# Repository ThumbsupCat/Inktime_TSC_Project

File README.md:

# Inktime_TSC_Project

## Cuprins:

1. Hardware: - Schematicul si pcb-ul
2. Manufacturing: - Bill of Materials si Pick & Place
3. Mechanical: fisierele 3D
4. Images: Imaginile cu produsul final

## Descriere
InkTime este un ceas smart optimizat pentru autonomie maximă și lizibilitate 
în lumina soarelui. MVP-ul include:

- Display e-paper 1.54" (200×200) cu refresh parțial o dată pe minut
- Notificări BLE de pe telefon cu alertă haptic
- Numărare pași în timp real prin accelerometru cu pedometru integrat
- Încărcare USB-C și programare prin Tag-Connect TC2030 SWD

## Arhitectură
Sistemul este construit în jurul MCU-ului **nRF52840** care integrează 
procesor ARM Cortex-M4 și radio BLE 5.0.
Alimentarea este asigurată de un charger LiPo **BQ25180** conectat la 
USB-C și un regulator buck-boost **RT6160** care menține 3.3V stabil 
pe toată gama de descărcare a bateriei.

## Schema Bloc

## Bill of Materials
| Ref | Component | Package | Funcție | LCSC | Datasheet |
|-----|-----------|---------|---------|------|-----------|
| U1 | nRF52840-QIAA | aQFN73 7×7mm | MCU + BLE 5.0 | [C190794](https://www.lcsc.com/product-detail/C190794.html) | [Datasheet](https://infocenter.nordicsemi.com/pdf/nRF52840_PS_v1.7.pdf) |
| IC1 | BQ25180YBGR | DSBGA-8 | Charger USB-C LiPo | [C3682423](https://www.lcsc.com/product-detail/C3682423.html)| [Datasheet](https://www.ti.com/lit/ds/symlink/bq25180.pdf) |
| IC9 | RT6160AWSC | WLCSP-15 | Regulator 3.3V buck-boost | [C7065276](https://www.lcsc.com/product-detail/C7065276.html) | [Datasheet](https://www.richtek.com/assets/product_file/RT6160A/DS6160A-00.pdf) |
| U3 | MAX17048G+T10 | DFN-8 2×2mm | Fuel gauge LiPo | [C2682616](https://www.lcsc.com/product-detail/C2682616.html) | [Datasheet](https://www.analog.com/media/en/technical-documentation/data-sheets/MAX17048-MAX17049.pdf) |
| IC3 | BMA421 | LGA-12 2×2mm | Accelerometru + pedometru | [C5242966](https://www.lcsc.com/product-detail/C5242966.html) | [Datasheet](https://www.bosch-sensortec.com/media/boschsensortec/downloads/datasheets/bst-bma421-ds000.pdf) |
| IC2 | DRV2605LDGSR | VSSOP-10 | Haptic driver ERM | [C527464](https://www.lcsc.com/product-detail/C527464.html) | [Datasheet](https://www.ti.com/lit/ds/symlink/drv2605l.pdf) |
| D3 | USBLC6-2SC6Y | SOT-363 | Protecție ESD USB | [C2687116](https://www.lcsc.com/product-detail/C2687116.html) | [Datasheet](https://www.st.com/resource/en/datasheet/usblc6-2.pdf) |
| Q1 | DMG2305UX-7 | SOT-323 | PFET EPD power gate | [C370432](https://www.lcsc.com/product-detail/C370432.html) | [Datasheet](https://www.diodes.com/assets/Datasheets/DMG2305UX.pdf) |
| Q3 | SI2301CDS | SOT-23 | PFET EPD gate control | [C10487](https://www.lcsc.com/product-detail/C10487.html) | [Datasheet](https://www.vishay.com/docs/70763/si2301cds.pdf) |
| J4 | KH-TYPE-C-16P | SMD | Conector USB-C | [C165948](https://www.lcsc.com/product-detail/C165948.html) | [Datasheet](https://datasheet.lcsc.com/lcsc/1912111437_Korean-Hroparts-Elec-TYPE-C-31-M-12_C165948.pdf) |
| J1 | 503480-2400 | SMD FPC | Conector display EPD 24 pini | [C393234](https://www.lcsc.com/product-detail/C393234.html) | [Datasheet](https://www.molex.com/pdm_docs/sd/5034802400_sd.pdf) |
| J2 | TC2030-IDC | PTH | Conector debug SWD Tag-Connect | - | [Datasheet](https://www.tag-connect.com/wp-content/uploads/bsk-pdf-manager/TC2030-IDC_1.pdf) |
| ANT1 | 2450AT18B100E | SMD | Antenă 2.4GHz BLE | - | [Datasheet](https://www.johansontechnology.com/datasheets/2450AT18B100E/2450AT18B100E.pdf) |
| L5 | WE-TPC 744042680 | 4828 | Inductor 68µH EPD boost | - | [Datasheet](https://www.we-online.com/catalog/datasheet/744042680.pdf) |
| L7 | FTC252012SR47MBCA | 0603 | Inductor 0.47µH RT6160 | - | - |
| X1 | NT2016SA-32MHz | 3225 | Crystal 32MHz MCU | - | - |
| X2 | Crystal 32.768kHz | 3215 | Crystal RTC | - | - |
| D2, D4, D5 | MBR0530T1G | SOD-123 | Diodă Schottky EPD driver | - | [Datasheet](https://www.onsemi.com/pdf/datasheet/mbr0530t1-d.pdf) |

## Pinii nRF52840

| Pin | Semnal | Componentă | Interfață |
|-----|--------|------------|-----------|
| P0.00/XL1 | XL1 | X2 32.768kHz crystal | Crystal RTC |
| P0.01/XL2 | XL2 | X2 32.768kHz crystal | Crystal RTC |
| P0.02 | SCK | EPD display | SPI |
| P0.03 | MOSI | EPD display | SPI |
| P0.05 | EPD_CS | EPD display | SPI CS |
| P0.06 | SDA | I2C bus (toți senzorii) | I2C |
| P0.07 | SCL | I2C bus (toți senzorii) | I2C |
| P0.08 | IMU_INT1 | BMA421 | GPIO interrupt |
| P0.12 | HAPTIC_EN | DRV2605L | GPIO enable |
| P0.13 | SW_UP | Buton UP | GPIO active-low |
| P0.14 | SW_DN | Buton DOWN | GPIO active-low |
| P0.15 | EPD_DC | EPD display | GPIO data/cmd |
| P0.16 | EPD_RST | EPD display | GPIO reset |
| P0.17 | EPD_BUSY | EPD display | GPIO busy |
| P0.18/RESET | RESET | TC2030 J2 | Hardware reset |
| P0.24 | SWDCLK | TC2030 J2 | SWD debug |
| P0.25 | SWDIO | TC2030 J2 | SWD debug |
| P1.00 | SW_ENT | Buton ENTER | GPIO active-low |
| P1.01 | EPD_3V3 gate | Q1 PFET | GPIO power gate EPD |
| P1.08 | IMU_INT2 | BMA421 | GPIO interrupt |
| VBUS | VBUS | J4 USB-C | USB 5V detect |
| D+ | DP | J4 USB-C | USB data+ |
| D- | DN | J4 USB-C | USB data- |
| ANT | RF | ANT1 2450AT18B100E | 2.4GHz BLE |

## Funcționalitate Hardware

### Power Path
USB-C (5V) → BQ25180 (charger + power path) → RT6160 (buck-boost 3.3V) → toți senzorii și MCU.
LiPo conectat la BQ25180 BAT. MAX17048 măsoară nivelul bateriei prin VBAT.
RT6160 menține 3.3V stabil pe toată gama de descărcare a bateriei (4.2V - 3.0V).

### MCU – nRF52840
Microcontroller ARM Cortex-M4 cu FPU, 64MHz, 1MB flash, 256KB RAM.
BLE 5.0 integrat cu antenă externă 2450AT18B100E plasată la exteriorul PCB-ului cu keepout sub ea.
Programare prin Tag-Connect TC2030 SWD (SWDIO, SWDCLK, RESET).

### Display E-Paper
Conector FPC 24 pini (J1) pentru panou e-paper 1.54" 200x200.
Comunicație SPI: SCK P0.02, MOSI P0.03, CS P0.05, DC P0.15, RST P0.16, BUSY P0.17.
Alimentare VEPD controlată prin PFET Q1 (gate P1.01) pentru power gating.
Circuit driver EPD: inductor L5 68µH, diode Schottky D2/D4/D5, condensatoare boost.

### IMU – BMA421
Accelerometru 3 axe cu pedometru integrat hardware.
Interfață I2C (adresă 0x18), INT1 pe P0.08 pentru wake-on-motion, INT2 pe P1.08.

### Haptic – DRV2605L
Driver motor ERM cu biblioteca de efecte haptic integrate.
Interfață I2C (adresă 0x5A), enable pe P0.12.
Motor ERM conectat direct la OUT+ și OUT-.

### Butoane
3 butoane tactile: UP (P0.13), DOWN (P0.14), ENTER (P1.00).
Configurație active-low cu pull-up intern activat în firmware.

### USB
Conector USB-C cu protecție ESD USBLC6 pe liniile D+/D-.
VBUS conectat la BQ25180 și la pinul de detecție al nRF52840.

### I2C Bus
Shared I2C pe SDA P0.06 / SCL P0.07 la 400kHz.
Dispozitive: BQ25180 (0x6A), RT6160 (0x75), MAX17048 (0x36), BMA421 (0x18), DRV2605L (0x5A).
Pull-up 10kΩ la 3.3V.

## PCB Design Notes

### Stackup
4 layere:
- Layer 1 (Top): semnal + componente SMD
- Layer 2: GND plane
- Layer 3: 3.3V power plane
- Layer 4 (Bottom): semnal

### Decizii de design
- GND rezolvat prin polygon pour pe toate layerele (Top, c2, Bottom)
- 3V3 rezolvat prin polygon pour pe layer-ul c63
- Antena 2450AT18B100E plasată la exteriorul boardului cu decupaj (keepout) 
  sub elementul radiant – fără cupru, fără trasee, fără plane sub antenă
- Condensatoare de decuplare plasate lângă pinii VCC ai fiecărui IC
- BMA421 plasat departe de motorul ERM pentru a evita false step counts
- Trasee de semnal: 0.15mm, trasee de power: 0.3mm

### Erori acceptate în DRC
- **Overlap Via-Smd - 6 erori approved**: via-uri în zona interioară a nRF52840 QFN73 
  din cauza densității extreme a pad-urilor. Nu pot fi rutate altfel in versiunea mea de rutare.
- **Copper Width - 2 erori approved**: trasee înguste (0.1mm) folosite pentru escape routing 
  din zona pinilor interiori ai MCU-ului unde spațiul nu permite 0.15mm.
- **Board Outline Clearance**: cauzate de modelul 3D al conectorului USB-C 
  care depășește ușor outline-ul – nu afectează fabricația.
- **Pad-Solid Polygon Shape, overlap**: footprintul pentru switchuri pe care l-am primit este facut prost.

### Probleme cunoscute
- Pinul RESET al nRF52840 rutat prin via escape din cauza
  poziției interioare în pachetul QFN73.
- Rutarea este foarte densă în zona nRF52840 din cauza 
  numărului mare de pini (73) și a spațiului limitat pe board.
  Acest lucru a necesitat trasee de 0.1mm și via-uri de escape
  pentru pinii din rândurile interioare ale chipului.

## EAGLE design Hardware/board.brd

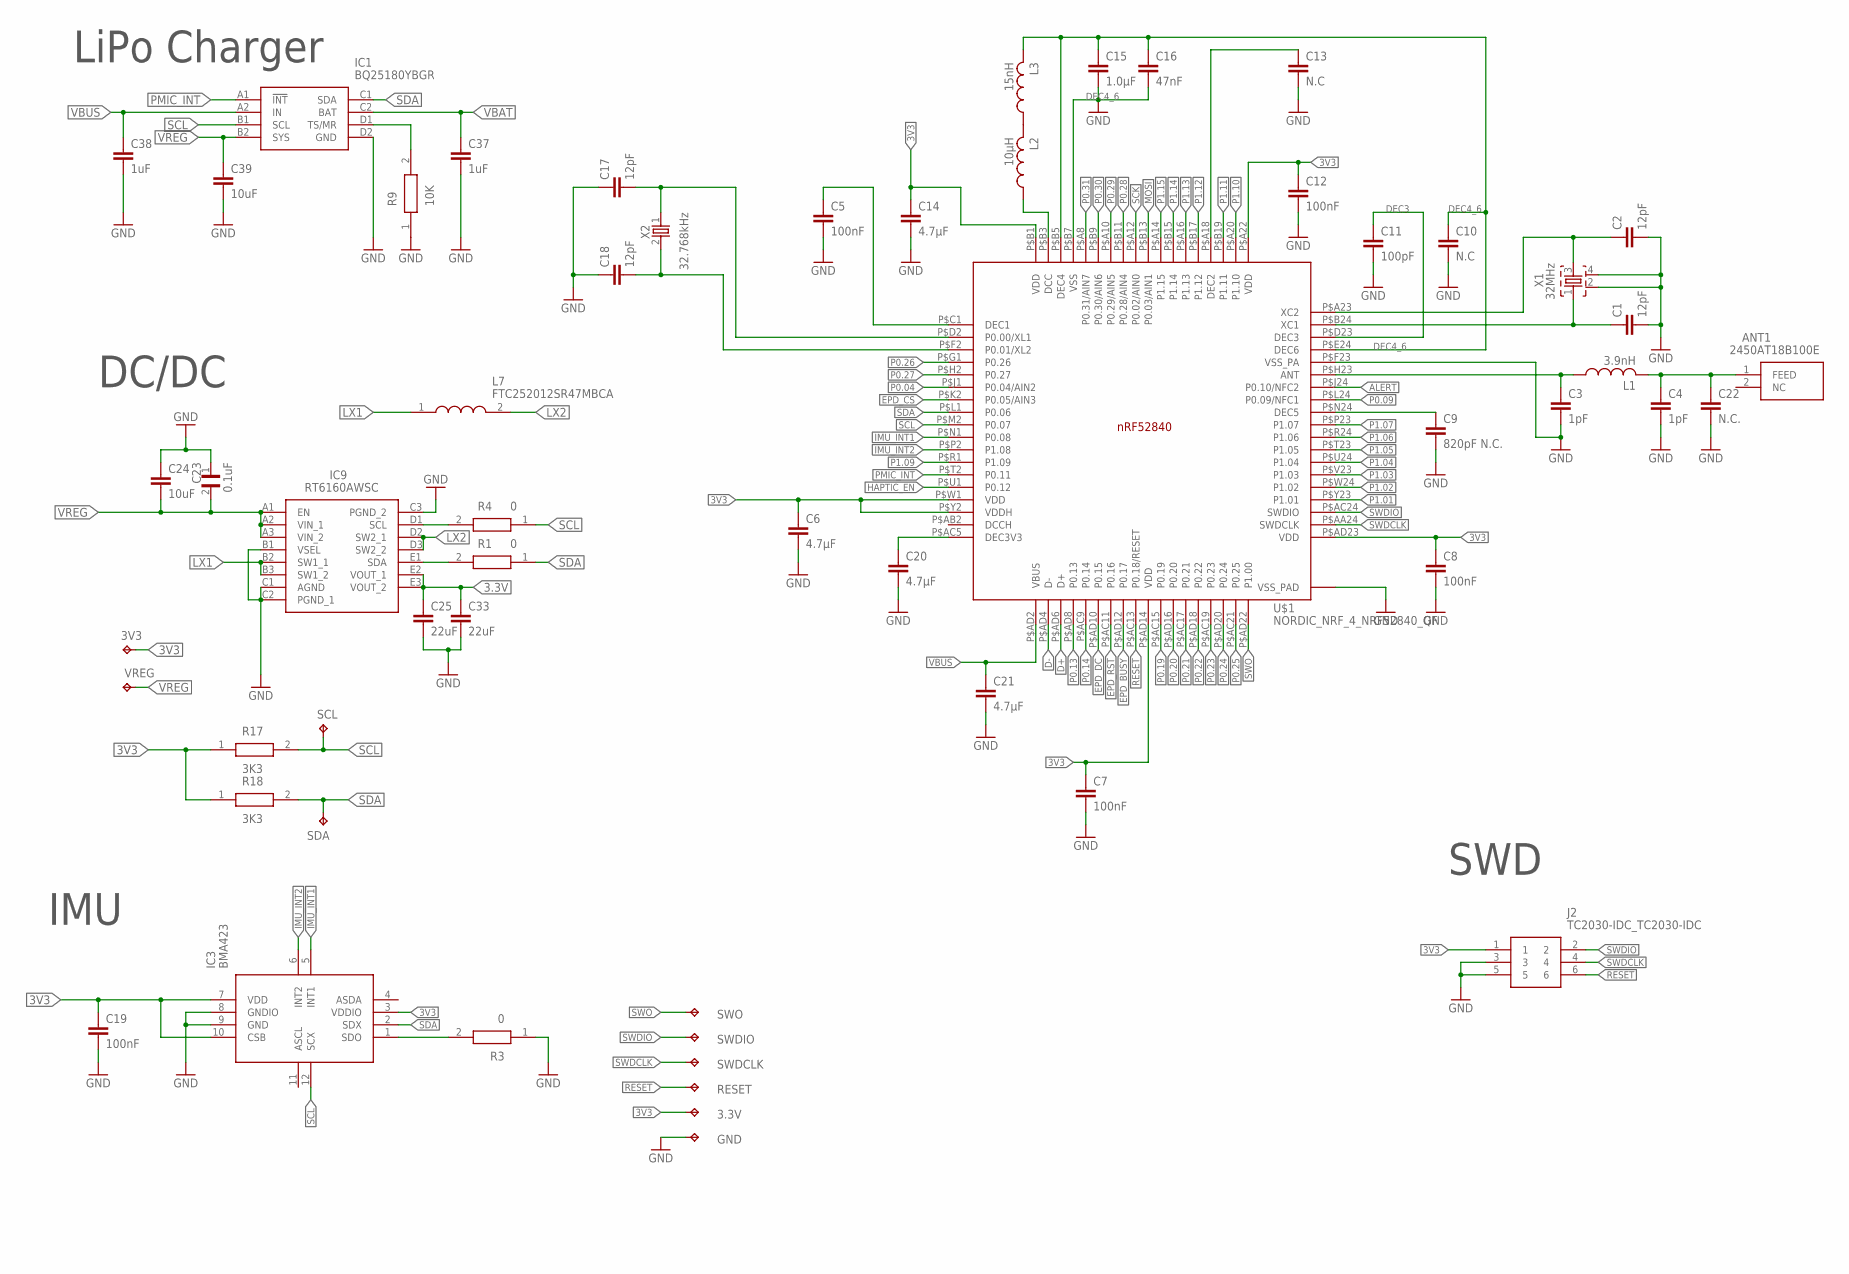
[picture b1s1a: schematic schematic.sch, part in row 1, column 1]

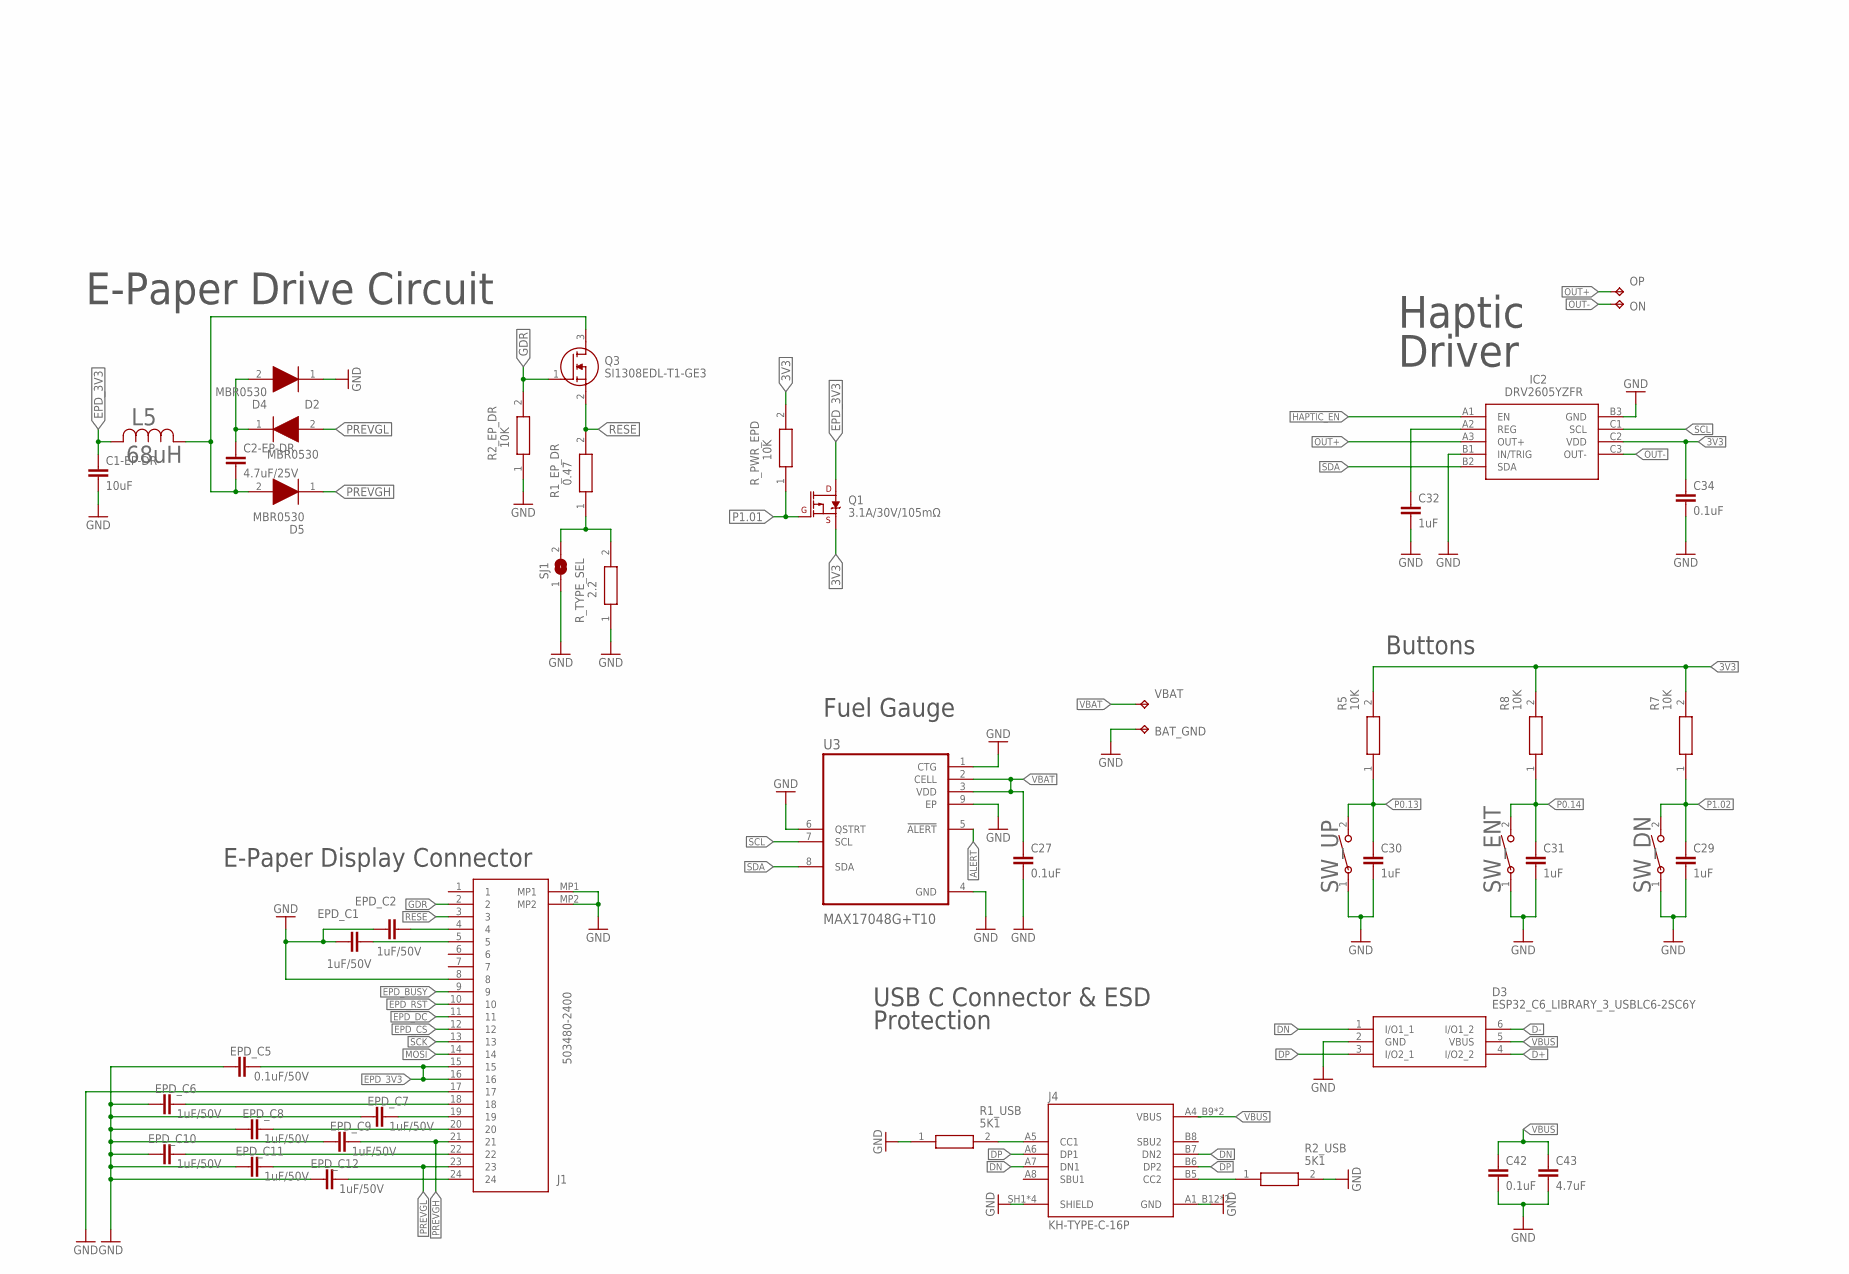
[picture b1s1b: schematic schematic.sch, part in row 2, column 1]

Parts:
3.3V, 3V3: HECTOR_WATCH_1_TPTP20R; HECTOR_WATCH_1_TP20R
ANT1: 2450AT18B100E; 2450AT18B100E_ANTC3216X140N
BAT_GND: HECTOR_WATCH_1_TPTP20R; HECTOR_WATCH_1_TP20R
C1, C2, C17, C18: 12pF; NORDIC_NRF_3_RESC0201_N
C1-EP-DR, C24, C39: 10uF; NORDIC_NRF_3_RESC0402_N
C2-EP-DR: 4.7uF/25V; NORDIC_NRF_3_RESC0402_N
C3, C4: 1pF; NORDIC_NRF_3_RESC0201_N
C5, C7, C8, C12, C19: 100nF; NORDIC_NRF_3_RESC0201_N
C6, C20, C21: 4.7µF; NORDIC_NRF_3_RESC0402_N
C9: 820pF N.C.; NORDIC_NRF_3_RESC0201_N
C10, C13: N.C; NORDIC_NRF_3_RESC0201_N
C11: 100pF; NORDIC_NRF_3_RESC0201_N
C14: 4.7µF; NORDIC_NRF_3_RESC0402_M
C15: 1.0µF; NORDIC_NRF_3_RESC0402_M
C16: 47nF; NORDIC_NRF_3_RESC0201_N
C22: N.C.; NORDIC_NRF_3_RESC0201_N
C23: 0.1uF; GRM011R60J152KE01L_1_0201
C25, C33: 22uF; NORDIC_NRF_3_RESC0402_N
C27, C34, C42: 0.1uF; NORDIC_NRF_3_RESC0201_N
C29, C30, C31, C32, C37, C38: 1uF; NORDIC_NRF_3_RESC0402_N
C43: 4.7uF; NORDIC_NRF_3_RESC0402_N
D2, D4, D5: MBR0530; ESP32_C6_LIBRARY_5_SOD3716X135N
D3: ESP32_C6_LIBRARY_3_USBLC6-2SC6Y; ESP32_C6_LIBRARY_3_SOT95P280X145-6N
EPD_C1, EPD_C2: 1uF/50V; NORDIC_NRF_3_RESC0402_N
EPD_C5: 0.1uF/50V; NORDIC_NRF_3_RESC0201_N
EPD_C6, EPD_C7, EPD_C8, EPD_C9, EPD_C10, EPD_C11, EPD_C12: 1uF/50V; ESP32_C6_LIBRARY_1_ESP32_WROVER_EAGLE-LTSPICE_C0402
GND: HECTOR_WATCH_1_TPTP20R; HECTOR_WATCH_1_TP20R
IC1: BQ25180YBGR; BQ25180YBGR_BGA8C40P2X4_100X155X50
IC2: DRV2605YZFR; DRV2605YZFR_BGA9C50P3X3_144X144X62
IC3: BMA423; BMA423_BMA423
IC9: RT6160AWSC; RT6160AWSC_BGA15C40P3X5_140X230X60
J1: 503480-2400; 503480-2400_5034802400
J2: TC2030-IDC_TC2030-IDC; TC2030-IDC_TC2030IDC
J4: KH-TYPE-C-16P; KH-TYPE-C-16P_KINGHELM_KH-TYPE-C-16P
L1: 3.9nH; NORDIC_NRF_2_RESC0402_N
L2: 10µH; NORDIC_NRF_2_RESC0603_N
L3: 15nH; NORDIC_NRF_2_RESC0402_N
L5: 68uH; ESP32_C6_LIBRARY_2_IND_4828-WE-TPC_WRE
L7: FTC252012SR47MBCA; MLP2016SR47MT0S1_INDC2016X100N
ON: HECTOR_WATCH_1_TPTP20R; HECTOR_WATCH_1_TP20R
OP: HECTOR_WATCH_1_TPTP20R; HECTOR_WATCH_1_TP20R
Q1: 3.1A/30V/105mΩ; ESP32_C6_LIBRARY_4_ESP32_C6_LIBRARY_4_ESP32_C6_LIBRARY_4_ES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
Q3: SI1308EDL-T1-GE3; ESP32_C6_LIBRARY_6_SOT65P210X110-3N
R1, R3, R4: 0; ERA-1AEB3401C_0201
R1_EP_DR: 0.47; CPF0201D7K68C1_0201
R1_USB, R2_USB: 5K1; ERA-1AEB3401C_0201
R2_EP_DR, R5, R8, R9: 10K; CPF0201D7K68C1_0201
R7: 10K; ERA-1AEB3401C_0201
R17, R18: 3K3; CPF0201D7K68C1_0201
RESET: HECTOR_WATCH_1_TPTP20R; HECTOR_WATCH_1_TP20R
R_PWR_EPD: 10K; ERA-1AEB3401C_0201
R_TYPE_SEL: 2.2; ERA-1AEB3401C_0201
SCL: HECTOR_WATCH_1_TPTP20R; HECTOR_WATCH_1_TP20R
SDA: HECTOR_WATCH_1_TPTP20R; HECTOR_WATCH_1_TP20R
SJ1: ESP32_C6_LIBRARY_7_JUMPER_SJ
SWDCLK: HECTOR_WATCH_1_TPTP20R; HECTOR_WATCH_1_TP20R
SWDIO: HECTOR_WATCH_1_TPTP20R; HECTOR_WATCH_1_TP20R
SWO: HECTOR_WATCH_1_TPTP20R; HECTOR_WATCH_1_TP20R
SW_DN: 2025-10-22_07-23-44_LIBRARY_EVP-AKE31ASW_EVP-AKE3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; 2025-10-22_07-23-44_LIBRARY_SW_EVP-AKE31A_PAN
SW_ENT: 2025-10-22_07-23-44_LIBRARY_EVP-AKE31ASW_EVP-AKE3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; 2025-10-22_07-23-44_LIBRARY_SW_EVP-AKE31A_PAN
SW_UP: 2025-10-22_07-23-44_LIBRARY_EVP-AKE31ASW_EVP-AKE3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; 2025-10-22_07-23-44_LIBRARY_SW_EVP-AKE31A_PAN
U3: MAX17048G+T10; ESP32_C6_LIBRARY_SON50P200X200X80-9N
U$1: NORDIC_NRF_4_NRF52840_QF; NORDIC_NRF_4_AQFN50P700X700X85_HS-74N
VBAT: HECTOR_WATCH_1_TPTP20R; HECTOR_WATCH_1_TP20R
VREG: HECTOR_WATCH_1_TPTP20R; HECTOR_WATCH_1_TP20R
X1: 32MHz; NORDIC_NRF_BT-XTAL_2016_N
X2: 32.768kHz; NORDIC_NRF_1_XTAL_3215_N

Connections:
3.3V: C25.1, C33.1, IC9.E2 (VOUT_1), IC9.E3 (VOUT_2)
3V3: 3.3V.TP, 3V3.TP, C6.1, C7.1, C8.1, C12.1, C14.1, C19.1, C34.1, IC2.C2 (VDD), IC3.3 (VDDIO), IC3.7 (VDD), IC3.10 (CSB), J2.1, Q1.2 (S), R5.2, R7.2, R8.2, R17.1, R18.1, R_PWR_EPD.2, U$1.P$A22 (VDD), U$1.P$AD14 (VDD), U$1.P$AD23 (VDD), U$1.P$B1 (VDD), U$1.P$W1 (VDD), U$1.P$Y2 (VDDH)
ALERT: U3.5 (!ALERT), U$1.P$J24 (P0.10/NFC2)
D+: D3.4 (I/O2_2), U$1.P$AD6 (D+)
D-: D3.6 (I/O1_2), U$1.P$AD4 (D-)
DEC3: C11.1, U$1.P$D23 (DEC3)
DEC4_6: C10.1, C15.1, C16.1, L3.2, U$1.P$B5 (DEC4), U$1.P$E24 (DEC6)
DN: D3.1 (I/O1_1), J4.A7 (DN1), J4.B7 (DN2)
DP: D3.3 (I/O2_1), J4.A6 (DP1), J4.B6 (DP2)
EPD_3V3: C1-EP-DR.1, EPD_C5.2, J1.15, J1.16, L5.2, Q1.3 (D)
EPD_BUSY: J1.9, U$1.P$AD12 (P0.17)
EPD_CS: J1.12, U$1.P$K2 (P0.05/AIN3)
EPD_DC: J1.11, U$1.P$AD10 (P0.15)
EPD_RST: J1.10, U$1.P$AC11 (P0.16)
GDR: J1.2, Q3.1 (G), R2_EP_DR.2
GND: BAT_GND.TP, C1.2, C1-EP-DR.2, C2.2, C3.2, C4.2, C5.2, C6.2, C7.2, C8.2, C9.2, C10.2, C11.2, C12.2, C13.2, C14.2, C15.2, C16.2, C17.1, C18.1, C19.2, C20.2, C21.2, C22.2, C23.1, C24.1, C25.2, C27.2, C29.2, C30.2, C31.2, C32.2, C33.2, C34.2, C37.2, C38.2, C39.2, C42.2, C43.2, D3.2 (GND), D4.1 (K), EPD_C1.1, EPD_C2.1, EPD_C5.1, EPD_C6.1, EPD_C7.1, EPD_C8.1, EPD_C9.1, EPD_C10.1, EPD_C11.1, EPD_C12.1, GND.TP, IC1.D2 (GND), IC2.B1 (IN/TRIG), IC2.B3 (GND), IC3.8 (GNDIO), IC3.9 (GND), IC9.B1 (VSEL), IC9.C1 (AGND), IC9.C2 (PGND_1), IC9.C3 (PGND_2), J1.8, J1.17, J1.MP1, J1.MP2, J2.3, J2.5, J4.A1_B12 (GND), J4.A12_B1 (GND), J4.SH1 (SHIELD), J4.SH2 (SHIELD), J4.SH3 (SHIELD), J4.SH4 (SHIELD), R1_USB.1, R2_EP_DR.1, R2_USB.2, R3.1, R9.1, R_TYPE_SEL.1, SJ1.1, SW_DN.1, SW_ENT.1, SW_UP.1, U3.1 (CTG), U3.4 (GND), U3.6 (QSTRT), U3.9 (EP), U$1.P$74 (VSS_PAD), U$1.P$75 (VSS_PAD), U$1.P$76 (VSS_PAD), U$1.P$77 (VSS_PAD), U$1.P$78 (VSS_PAD), U$1.P$79 (VSS_PAD), U$1.P$80 (VSS_PAD), U$1.P$81 (VSS_PAD), U$1.P$82 (VSS_PAD), U$1.P$83 (VSS_PAD), U$1.P$84 (VSS_PAD), U$1.P$85 (VSS_PAD), U$1.P$86 (VSS_PAD), U$1.P$87 (VSS_PAD), U$1.P$88 (VSS_PAD), U$1.P$89 (VSS_PAD), U$1.P$90 (VSS_PAD), U$1.P$B7 (VSS), U$1.P$F23 (VSS_PA), X1.2, X1.4
HAPTIC_EN: IC2.A1 (EN), U$1.P$U1 (P0.12)
IMU_INT1: IC3.5 (INT1), U$1.P$N1 (P0.08)
IMU_INT2: IC3.6 (INT2), U$1.P$P2 (P1.08)
LX1: IC9.B2 (SW1_1), IC9.B3 (SW1_2), L7.1
LX2: IC9.D2 (SW2_1), IC9.D3 (SW2_2), L7.2
MOSI: J1.14, U$1.P$B13 (P0.03/AIN1)
unnamed: C5.1, U$1.P$C1 (DEC1)
unnamed: C17.2, U$1.P$D2 (P0.00/XL1), X2.1
unnamed: IC1.D1 (TS/MR), R9.2
unnamed: C18.2, U$1.P$F2 (P0.01/XL2), X2.2
unnamed: L2.1, U$1.P$B3 (DCC)
unnamed: IC9.D1 (SCL), R4.2
unnamed: C20.1, U$1.P$AC5 (DEC3V3)
unnamed: IC9.E1 (SDA), R1.2
unnamed: IC3.1 (SDO), R3.2
unnamed: L2.2, L3.1
unnamed: C13.1, U$1.P$A18 (DEC2)
unnamed: C2.1, U$1.P$A23 (XC2), X1.3
unnamed: C1.1, U$1.P$B24 (XC1), X1.1
unnamed: ANT1.1 (FEED), C4.1, C22.1, L1.2
unnamed: C3.1, L1.1, U$1.P$H23 (ANT)
unnamed: C2-EP-DR.2, D5.2 (A), L5.1, Q3.3 (D)
unnamed: C2-EP-DR.1, D2.1 (K), D4.2 (A)
unnamed: C9.1, U$1.P$N24 (DEC5)
unnamed: R1_EP_DR.1, R_TYPE_SEL.2, SJ1.2
unnamed: EPD_C12.2, J1.24
unnamed: EPD_C6.2, J1.18
unnamed: J4.A5 (CC1), R1_USB.2
unnamed: C32.1, IC2.A2 (REG)
unnamed: EPD_C10.2, J1.22
unnamed: J4.B5 (CC2), R2_USB.1
unnamed: EPD_C8.2, J1.20
unnamed: EPD_C7.2, J1.19
unnamed: EPD_C2.2, J1.4
unnamed: EPD_C1.2, J1.5
OUT+: IC2.A3 (OUT+), OP.TP
OUT-: IC2.C3 (OUT-), ON.TP
P0.04: U$1.P$J1 (P0.04/AIN2)
P0.09: U$1.P$L24 (P0.09/NFC1)
P0.13: C30.1, R5.1, SW_UP.2, U$1.P$AD8 (P0.13)
P0.14: C31.1, R8.1, SW_ENT.2, U$1.P$AC9 (P0.14)
P0.19: U$1.P$AC15 (P0.19)
P0.20: U$1.P$AD16 (P0.20)
P0.21: U$1.P$AC17 (P0.21)
P0.22: U$1.P$AD18 (P0.22)
P0.23: U$1.P$AC19 (P0.23)
P0.24: U$1.P$AD20 (P0.24)
P0.25: U$1.P$AC21 (P0.25)
P0.26: U$1.P$G1 (P0.26)
P0.27: U$1.P$H2 (P0.27)
P0.28: U$1.P$B11 (P0.28/AIN4)
P0.29: U$1.P$A10 (P0.29/AIN5)
P0.30: U$1.P$B9 (P0.30/AIN6)
P0.31: U$1.P$A8 (P0.31/AIN7)
P1.01: Q1.1 (G), R_PWR_EPD.1, U$1.P$Y23 (P1.01)
P1.02: C29.1, R7.1, SW_DN.2, U$1.P$W24 (P1.02)
P1.03: U$1.P$V23 (P1.03)
P1.04: U$1.P$U24 (P1.04)
P1.05: U$1.P$T23 (P1.05)
P1.06: U$1.P$R24 (P1.06)
P1.07: U$1.P$P23 (P1.07)
P1.09: U$1.P$R1 (P1.09)
P1.10: U$1.P$A20 (P1.10)
P1.11: U$1.P$B19 (P1.11)
P1.12: U$1.P$B17 (P1.12)
P1.13: U$1.P$A16 (P1.13)
P1.14: U$1.P$B15 (P1.14)
P1.15: U$1.P$A14 (P1.15)
PMIC_INT: IC1.A1 (!INT), U$1.P$T2 (P0.11)
PREVGH: D5.1 (K), EPD_C9.2, J1.21
PREVGL: D2.2 (A), EPD_C11.2, J1.23
RESE: J1.3, Q3.2 (S), R1_EP_DR.2
RESET: J2.6, RESET.TP, U$1.P$AC13 (P0.18/RESET)
SCK: J1.13, U$1.P$A12 (P0.02/AIN0)
SCL: IC1.B1 (SCL), IC2.C1 (SCL), IC3.12 (SCX), R4.1, R17.2, SCL.TP, U3.7 (SCL), U$1.P$M2 (P0.07)
SDA: IC1.C1 (SDA), IC2.B2 (SDA), IC3.2 (SDX), R1.1, R18.2, SDA.TP, U3.8 (SDA), U$1.P$L1 (P0.06)
SWDCLK: J2.4, SWDCLK.TP, U$1.P$AA24 (SWDCLK)
SWDIO: J2.2, SWDIO.TP, U$1.P$AC24 (SWDIO)
SWO: SWO.TP, U$1.P$AD22 (P1.00)
VBAT: C27.1, C37.1, IC1.C2 (BAT), U3.2 (CELL), U3.3 (VDD), VBAT.TP
VBUS: C21.1, C38.1, C42.1, C43.1, D3.5 (VBUS), IC1.A2 (IN), J4.A4_B9 (VBUS), J4.A9_B4 (VBUS), U$1.P$AD2 (VBUS)
VREG: C23.2, C24.2, C39.1, IC1.B2 (SYS), IC9.A1 (EN), IC9.A2 (VIN_1), IC9.A3 (VIN_2), VREG.TP

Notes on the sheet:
LiPo Charger
DC/DC
IMU
SWD
E-Paper Drive Circuit
Haptic Driver
E-Paper Display Connector
Fuel Gauge
Buttons
USB C Connector & ESD Protection

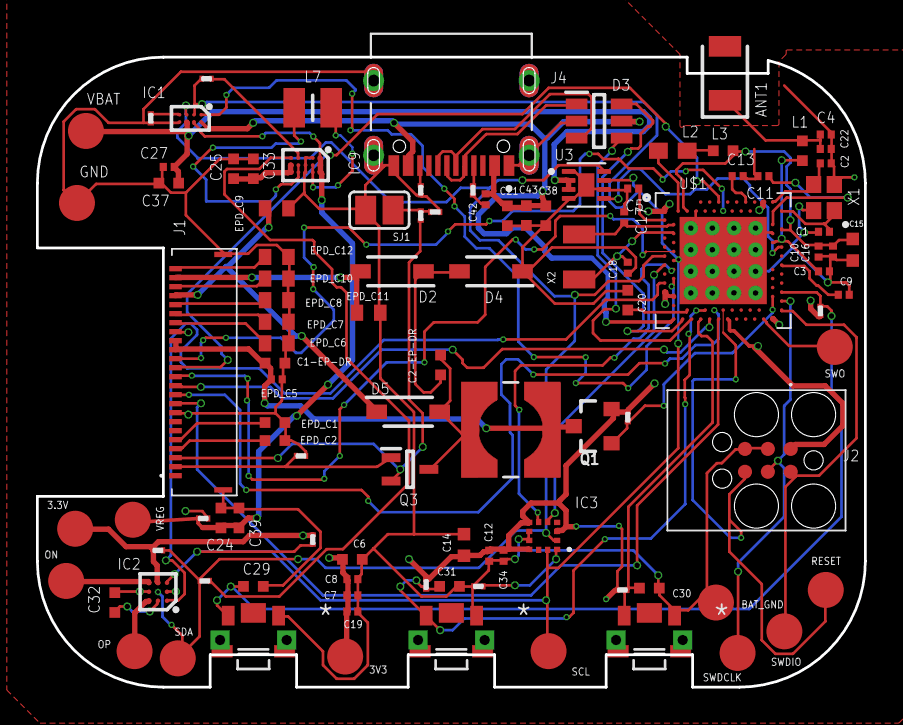
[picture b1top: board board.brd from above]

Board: 4 copper layers, 46.0 x 35.0 mm, 105 parts (0 on the bottom side), 71 nets.

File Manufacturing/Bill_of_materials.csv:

Reference Designators;Quantity;Description;Package;Value;Manufacturer;Manufacturer Part Number;Vendor;Vendor Part Number;Top/Bottom;
;1;PCB Board;Board;;;;;;;
ANT1;1;Antennas 2.45GHz ANTENNA;2450AT18B100E_ANTC3216X140N;2450AT18B100E;;;;;Top;
C1, C2, C17, C18;4;Generic chip capacitor;NORDIC_NRF_3_RESC0201_N;12pF;;;;;Top;
C1-EP-DR, C24, C39;3;Generic chip capacitor;NORDIC_NRF_3_RESC0402_N;10uF;;;;;Top;
C2-EP-DR;1;Generic chip capacitor;NORDIC_NRF_3_RESC0402_N;4.7uF/25V;;;;;Top;
C3, C4;2;Generic chip capacitor;NORDIC_NRF_3_RESC0201_N;1pF;;;;;Top;
C5, C7, C8, C12, C19;5;Generic chip capacitor;NORDIC_NRF_3_RESC0201_N;100nF;;;;;Top;
C6, C20, C21;3;Generic chip capacitor;NORDIC_NRF_3_RESC0402_N;4.7µF;;;;;Top;
C9;1;Generic chip capacitor;NORDIC_NRF_3_RESC0201_N;820pF N.C.;;;;;Top;
C10, C13;2;Generic chip capacitor;NORDIC_NRF_3_RESC0201_N;N.C;;;;;Top;
C11;1;Generic chip capacitor;NORDIC_NRF_3_RESC0201_N;100pF;;;;;Top;
C14;1;Generic chip capacitor;NORDIC_NRF_3_RESC0402_M;4.7µF;;;;;Top;
C15;1;Generic chip capacitor;NORDIC_NRF_3_RESC0402_M;1.0µF;;;;;Top;
C16;1;Generic chip capacitor;NORDIC_NRF_3_RESC0201_N;47nF;;;;;Top;
C22;1;Generic chip capacitor;NORDIC_NRF_3_RESC0201_N;N.C.;;;;;Top;
C23;1;Check availability;CAPC0201X13N;0.1uF;;;;;Top;
C25, C33;2;Generic chip capacitor;NORDIC_NRF_3_RESC0402_N;22uF;;;;;Top;
C27, C34, C42;3;Generic chip capacitor;NORDIC_NRF_3_RESC0201_N;0.1uF;;;;;Top;
C29, C30, C31, C32, C37, C38;6;Generic chip capacitor;NORDIC_NRF_3_RESC0402_N;1uF;;;;;Top;
C43;1;Generic chip capacitor;NORDIC_NRF_3_RESC0402_N;4.7uF;;;;;Top;
D1;1;Low Cap. ESD Protection Auto SOT-23-6 STMicroelectronics USBLC6-2SC6Y, Dual Uni-Directional TVS Diode Array, 6-Pin SOT-23;SOT95P280X145-6N;ESP32_C6_LIBRARY_3_USBLC6-2SC6Y;;;;;Top;
D2, D4, D5;3;ON SEMICONDUCTOR - MBR0530 - DIODE, SCHOTTKY, 0.5A, 30V, SOD-123;SOD3716X135N;MBR0530;;;;;Top;
EPD_C1, EPD_C2;2;Generic chip capacitor;NORDIC_NRF_3_RESC0402_N;1uF/50V;;;;;Top;
EPD_C5;1;Generic chip capacitor;NORDIC_NRF_3_RESC0201_N;0.1uF/50V;;;;;Top;
EPD_C6, EPD_C7, EPD_C8, EPD_C9, EPD_C10, EPD_C11, EPD_C12;7;CAPACITOR, European symbol;ESP32_WROVER_EAGLE-LTSPICE_C0402;1uF/50V;;;;;Top;
IC1;1;Charger IC Lithium Ion/Polymer, Lithium Iron Phosphate 8-DSBGA (1.6x1.1);BQ25180YBGR_BGA8C40P2X4_100X155X50;BQ25180YBGR;;;;;Top;
IC2;1;Haptic Driver for ERM/LRA with Built-In Library and Smart Loop Architecture;DRV2605YZFR_BGA9C50P3X3_144X144X62;DRV2605YZFR;;;;;Top;
IC3;1;Accelerometers Triaxial low-g 12bit Acceleration Sensor;BMA423_BMA423;BMA423;;;;;Top;
IC9;1;Buck-Boost Regulator Positive Output Step-Up/Step-Down I2C DC-DC Controller IC 15-WL-CSP (BSC) (1.4x2.3);RT6160AWSC_BGA15C40P3X5_140X230X60;RT6160AWSC;;;;;Top;
J1;1;FFC & FPC Connectors 0.5mm FPC RA SMT Dual Contact 24Ckt;503480-2400_5034802400;503480-2400;;;;;Top;
J2;1;CABLE ADAPTER 6 POS;TC2030-IDC_TC2030IDC;TC2030-IDC_TC2030-IDC;;;;;Top;
J4;1;Check availability;KINGHELM_KH-TYPE-C-16P;KH-TYPE-C-16P;;;;;Top;
L1;1;Generic chip inductor;NORDIC_NRF_2_RESC0402_N;3.9nH;;;;;Top;
L2;1;Generic chip inductor;NORDIC_NRF_2_RESC0603_N;10µH;;;;;Top;
L3;1;Generic chip inductor;NORDIC_NRF_2_RESC0402_N;15nH;;;;;Top;
L5;1;;ESP32_C6_LIBRARY_2_IND_4828-WE-TPC_WRE;68uH;;;;;Top;
L7;1;SMD / SMT Inductors (Coils), L=0.47?H, L x W x T :;MLP2016SR47MT0S1_INDC2016X100N;FTC252012SR47MBCA;;;;;Top;
Q1;1;MOSFET N-Ch 30V 1.5A TrenchFET SC70 Vishay Si1308EDL-T1-GE3 N-channel MOSFET Transistor, 1.5 A, 30 V, 3-Pin SC-70;SOT65P210X110-3N;SI1308EDL-T1-GE3;;;;;Top;
Q2;1;P-channel MOSFETs;ESP32_WROVER_SPARKFUN-DISCRETESEMI_SOT23-3;3.1A/30V/105mΩ;;;;;Top;
R_PWR_EPD, R7;2;7.68k 0201 Thin Film Surface Mount Fixed Resistor +/-0.5% 0.031W CPF0201D7K68C1;R0201;10K;;;;;Top;
R_TYPE_SEL;1;7.68k 0201 Thin Film Surface Mount Fixed Resistor +/-0.5% 0.031W CPF0201D7K68C1;R0201;2.2;;;;;Top;
R1, R3, R4;3;7.68k 0201 Thin Film Surface Mount Fixed Resistor +/-0.5% 0.031W CPF0201D7K68C1;R0201;0;;;;;Top;
R1_EP_DR;1;7.68k 0201 Thin Film Surface Mount Fixed Resistor +/-0.5% 0.031W CPF0201D7K68C1;CPF0201D7K68C1_0201;0.47;;;;;Top;
R1_USB, R2_USB;2;7.68k 0201 Thin Film Surface Mount Fixed Resistor +/-0.5% 0.031W CPF0201D7K68C1;R0201;5K1;;;;;Top;
R2_EP_DR, R5, R8, R9;4;7.68k 0201 Thin Film Surface Mount Fixed Resistor +/-0.5% 0.031W CPF0201D7K68C1;CPF0201D7K68C1_0201;10K;;;;;Top;
R17, R18;2;7.68k 0201 Thin Film Surface Mount Fixed Resistor +/-0.5% 0.031W CPF0201D7K68C1;CPF0201D7K68C1_0201;3K3;;;;;Top;
SJ1;1;SMD solder JUMPER;JUMPER_SJ;;;;;;Top;
SW_DN, SW_ENT, SW_UP;3;;SW_EVP-AKE31A_PAN;2025-10-22_07-23-44_LIBRARY_EVP-AKE31ASW_EVP-AKE31A_PAN;;;;;Top;
TP_3.3V, TP_3V3, TP_BAT_GND, TP_GND, TP_ON, TP_OP, TP_RESET, TP_SCL, TP_SDA, TP_SWDCLK, TP_SWDIO, TP_SWO, TP_VBAT, TP_VREG;14;Test pad;HECTOR_WATCH_1_TP20R;HECTOR_WATCH_1_TPTP20R;;;;;Top;
U1;1;nRF52840;NORDIC_NRF_4_AQFN50P700X700X85_HS-74N;NRF52840_QF;;;;;Top;
U3;1;Check availability;SON50P200X200X80-9N;MAX17048G+T10;;;;;Top;
X1;1;;NORDIC_NRF_BT-XTAL_2016_N;32MHz;;;;;Top;
X2;1;;NORDIC_NRF_1_XTAL_3215_N;32.768kHz;;;;;Top;

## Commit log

2026-04-10 Add files via upload
    Added schematic and board files
2026-04-10 moved board.brd to Hardware/board.brd
2026-04-10 moved schematic.sch to Hardware/schematic.sch
2026-04-10 Add files via upload
    Todo
2026-04-10 Create Mechanical/.dummy
    To be done
2026-04-10 Update README with project details and table of contents
    Added a table of contents and additional project details.
2026-04-21 Schematic and 2D PCB updated to final version
2026-04-21 Images added
2026-04-21 Revise README with project overview and details
    Updated the README to include project details, architecture, and hardware functionality.
2026-04-21 README fixed diagram block not showing
2026-04-21 Manufacturing and mechanical files uploaded, dummies deleted

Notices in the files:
parts and their libraries:
COPYRIGHT: Copyright (C) 2024 Ultra Librarian. All rights reserved.
COPYRIGHT: Copyright (C) 2025 Ultra Librarian. All rights reserved.
